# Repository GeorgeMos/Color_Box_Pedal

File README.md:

# Color_Box_Pedal
Color_Box_Pedal
The files are part of a complete KiCad project.
The .rar file contains all the necessary files for the pcb production.
Any one ia free to make this pedal.
Is is prefered not to use the same name and i would love to be referenced in the clone design.

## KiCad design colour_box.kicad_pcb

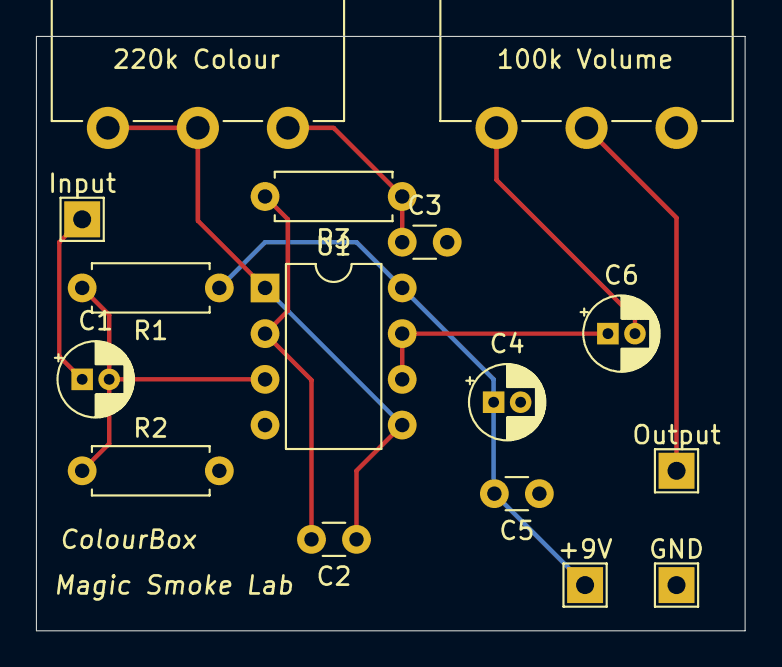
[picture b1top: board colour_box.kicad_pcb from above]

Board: 2 copper layers, 39.4 x 33.0 mm, 16 parts (0 on the bottom side), 10 nets.

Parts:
100k Volume: 100k_Volume; Potentiometer_Piher_PC-16_Single_Vertical
220k Colour: 220k_Filter; Potentiometer_Piher_PC-16_Single_Vertical
+9V: TestPoint_THTPad_2.0x2.0mm_Drill1.0mm
C1: 2.2u; CP_Radial_D4.0mm_P1.50mm
C2: 100p; C_Disc_D3.0mm_W1.6mm_P2.50mm
C3, C5: 0.1u; C_Disc_D3.0mm_W1.6mm_P2.50mm
C4: 10u; CP_Radial_D4.0mm_P1.50mm
C6: 0.1u; CP_Radial_D4.0mm_P1.50mm
GND: TestPoint_THTPad_2.0x2.0mm_Drill1.0mm
Input: TestPoint_THTPad_2.0x2.0mm_Drill1.0mm
Output: TestPoint_THTPad_2.0x2.0mm_Drill1.0mm
R1, R2: 10k; R_Axial_DIN0207_L6.3mm_D2.5mm_P7.62mm_Horizontal
R3: 100k; R_Axial_DIN0207_L6.3mm_D2.5mm_P7.62mm_Horizontal
U1: TL072; DIP-8_W7.62mm

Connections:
+9V: +9V.1, C4.1, C5.2, R1.1, U1.8
GND: 100k Volume.1, C3.2, C4.2, C5.1, GND.1, R2.2, U1.4
Input: C1.1, Input.1
unnamed: C1.2, R1.2, R2.1, U1.3
unnamed: 220k Colour.2, 220k Colour.3, C2.1, U1.1, U1.5
unnamed: C2.2, R3.2, U1.2
unnamed: 220k Colour.1, C3.1, R3.1
unnamed: C6.1, U1.6, U1.7
unnamed: 100k Volume.3, C6.2
Output: 100k Volume.2, Output.1
